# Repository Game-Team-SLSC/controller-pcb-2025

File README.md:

# Game Team's controller PCB for Eurobot Junior 2025

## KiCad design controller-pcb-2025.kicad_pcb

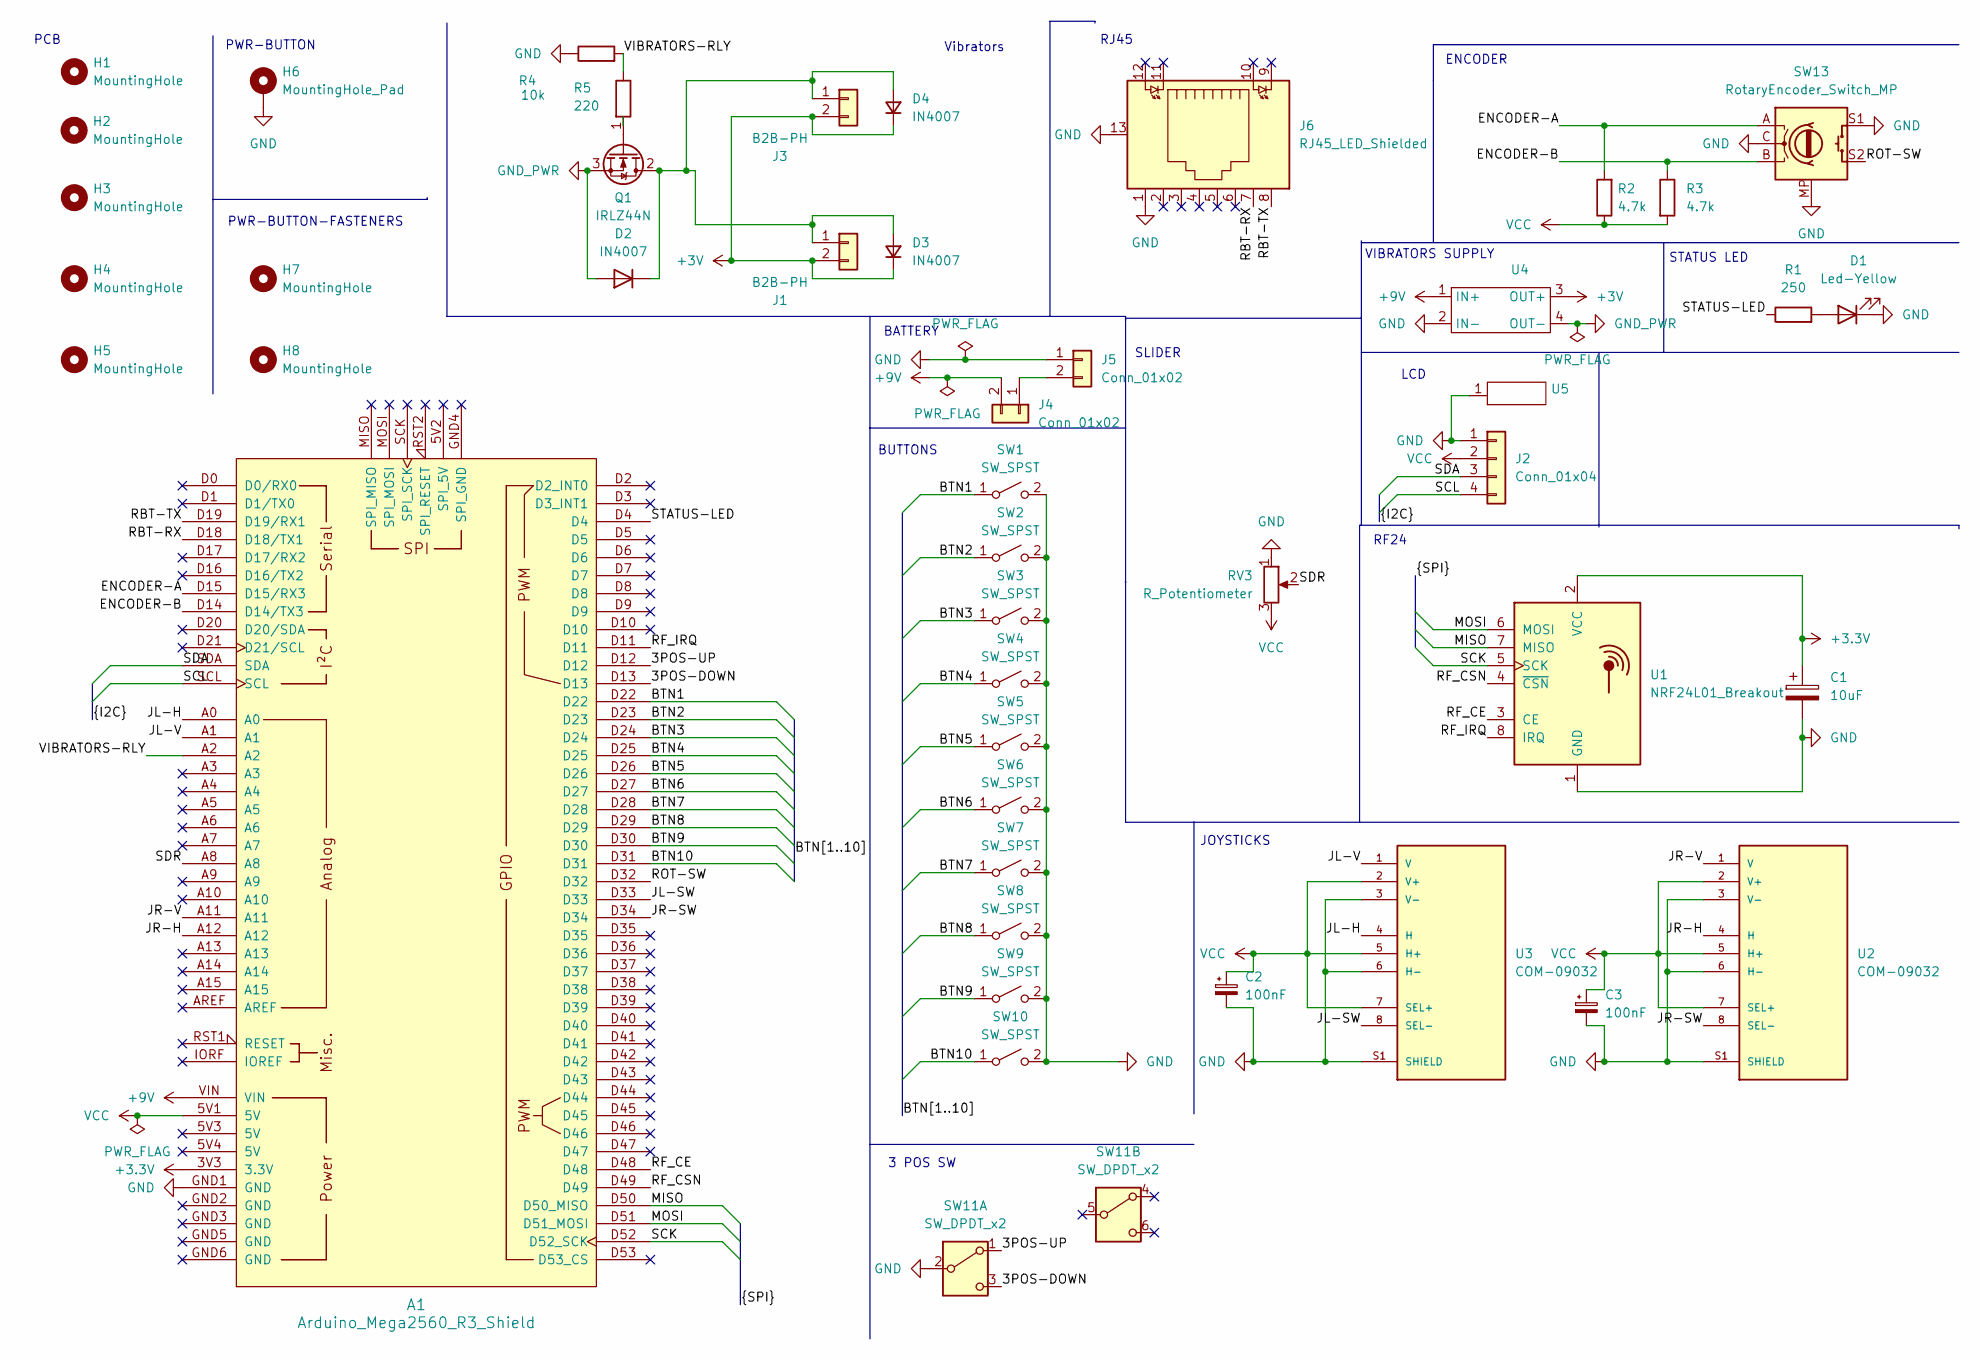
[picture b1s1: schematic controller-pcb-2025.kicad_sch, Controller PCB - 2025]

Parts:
A1: Arduino_Mega2560_R3_Shield; Arduino_Mega2560_R3_Shield_No-MH
C1: 10uF; CP_Radial_D5.0mm_P2.00mm
C2, C3: 100nF
D1: Led-Yellow; LED_D5.0mm
D2: IN4007; D_A-405_P7.62mm_Horizontal
D3, D4: IN4007
H1, H2, H3, H4, H5, H7, H8: MountingHole; MountingHole_2.7mm_M2.5
H6: MountingHole_Pad; Pwr-button_LED
J1, J3: B2B-PH; JST_PH_B2B-PH-K_1x02_P2.00mm_Vertical
J2: Conn_01x04; JST_PH_B4B-PH-K_1x04_P2.00mm_Vertical
J4: Conn_01x02; JST_PH_B2B-PH-K_1x02_P2.00mm_Vertical
J5: Conn_01x02; AMASS_XT30UPB-M_1x02_P5.0mm_Vertical
J6: RJ45_LED_Shielded; RJ45_Cetus_J1B1211CCD_Horizontal-3D-model
Q1: IRLZ44N; TO-220-3_Horizontal_TabDown
R1: 250; R_Axial_DIN0207_L6.3mm_D2.5mm_P7.62mm_Horizontal
R2, R3: 4.7k; R_Axial_DIN0207_L6.3mm_D2.5mm_P7.62mm_Horizontal
R4: 10k; R_Axial_DIN0207_L6.3mm_D2.5mm_P7.62mm_Horizontal
R5: 220; R_Axial_DIN0207_L6.3mm_D2.5mm_P7.62mm_Horizontal
RV3: R_Potentiometer; F2031N
SW1, SW2, SW3, SW4, SW5, SW6, SW7, SW8, SW9, SW10: SW_SPST; ADA1502
SW11: SW_DPDT_x2; KCD2
SW13: RotaryEncoder_Switch_MP; RotaryEncoder_Alps_EC11E-Switch_Vertical_H20mm-3D-model
U1: NRF24L01_Breakout; nRF24L01+_Breakout
U2, U3: COM-09032; XDCR_COM-09032; PARTREV N/A
U4: LM2596
U5: DFR0555

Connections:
+3.3V: A1.3V3 (3.3V), C1.1, U1.2 (VCC)
+3V: D3.1 (K), D4.1 (K), J1.2, J3.2, U4.3 (OUT+)
+9V: A1.VIN, J4.2, U4.1 (IN+)
/3POS-DOWN: A1.D13, SW11.3 (C)
/3POS-UP: A1.D12, SW11.1 (A)
/BTN1: A1.D22, SW1.1 (A)
/BTN2: A1.D23, SW2.1 (A)
/BTN3: A1.D24, SW3.1 (A)
/BTN4: A1.D25, SW4.1 (A)
/BTN5: A1.D26, SW5.1 (A)
/BTN6: A1.D27, SW6.1 (A)
/BTN7: A1.D28, SW7.1 (A)
/BTN8: A1.D29, SW8.1 (A)
/BTN9: A1.D30, SW9.1 (A)
/BTN10: A1.D31, SW10.1 (A)
/ENCODER-A: A1.D15 (D15/RX3), R2.2, SW13.A
/ENCODER-B: A1.D14 (D14/TX3), R3.1, SW13.B
/JL-H: A1.A0, U3.4 (H)
/JL-SW: A1.D33, U3.8 (SEL-)
/JL-V: A1.A1, U3.1 (V)
/JR-H: A1.A12, U2.4 (H)
/JR-SW: A1.D34, U2.8 (SEL-)
/JR-V: A1.A11, U2.1 (V)
/MISO: A1.D50 (D50_MISO), U1.7 (MISO)
/MOSI: A1.D51 (D51_MOSI), U1.6 (MOSI)
/RBT-RX: A1.D18 (D18/TX1), J6.7
/RBT-TX: A1.D19 (D19/RX1), J6.8
/RF_CE: A1.D48, U1.3 (CE)
/RF_CSN: A1.D49, U1.4 (~CSN)
/RF_IRQ: A1.D11, U1.8 (IRQ)
/ROT-SW: A1.D32, SW13.S2
/SCK: A1.D52 (D52_SCK), U1.5 (SCK)
/SCL: A1.SCL, J2.4
/SDA: A1.SDA, J2.3
/SDR: A1.A8, RV3.2
/STATUS-LED: A1.D4, R1.1
/VIBRATORS-RLY: A1.A2, R4.2, R5.1
unnamed: D1.2 (A), R1.2
unnamed: D2.1 (K), D3.2 (A), D4.2 (A), J1.1, J3.1, Q1.2 (D)
unnamed: J4.1, J5.2
unnamed: Q1.1 (G), R5.2
VCC: A1.5V1 (5V), C2.1, C3.1, J2.2, R2.1, R3.2, RV3.3, U2.2 (V+), U2.5 (H+), U2.7 (SEL+), U3.2 (V+), U3.5 (H+), U3.7 (SEL+)

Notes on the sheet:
PWR-BUTTON
BUTTONS
BATTERY
3 POS SW
Vibrators
LCD
PCB
VIBRATORS SUPPLY
PWR-BUTTON-FASTENERS
RJ45
RF24
JOYSTICKS
SLIDER
ENCODER
STATUS LED

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
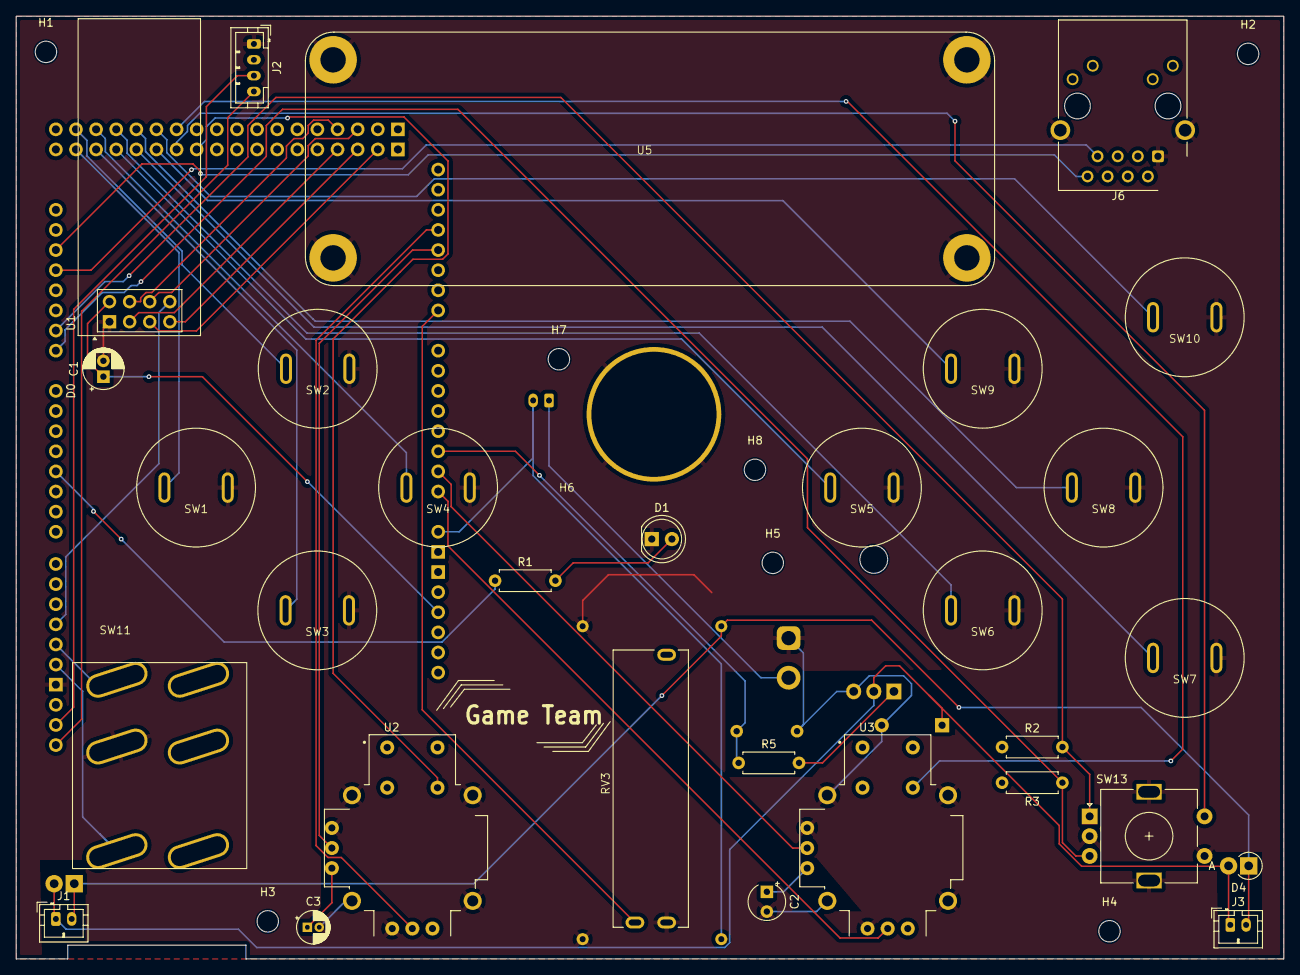
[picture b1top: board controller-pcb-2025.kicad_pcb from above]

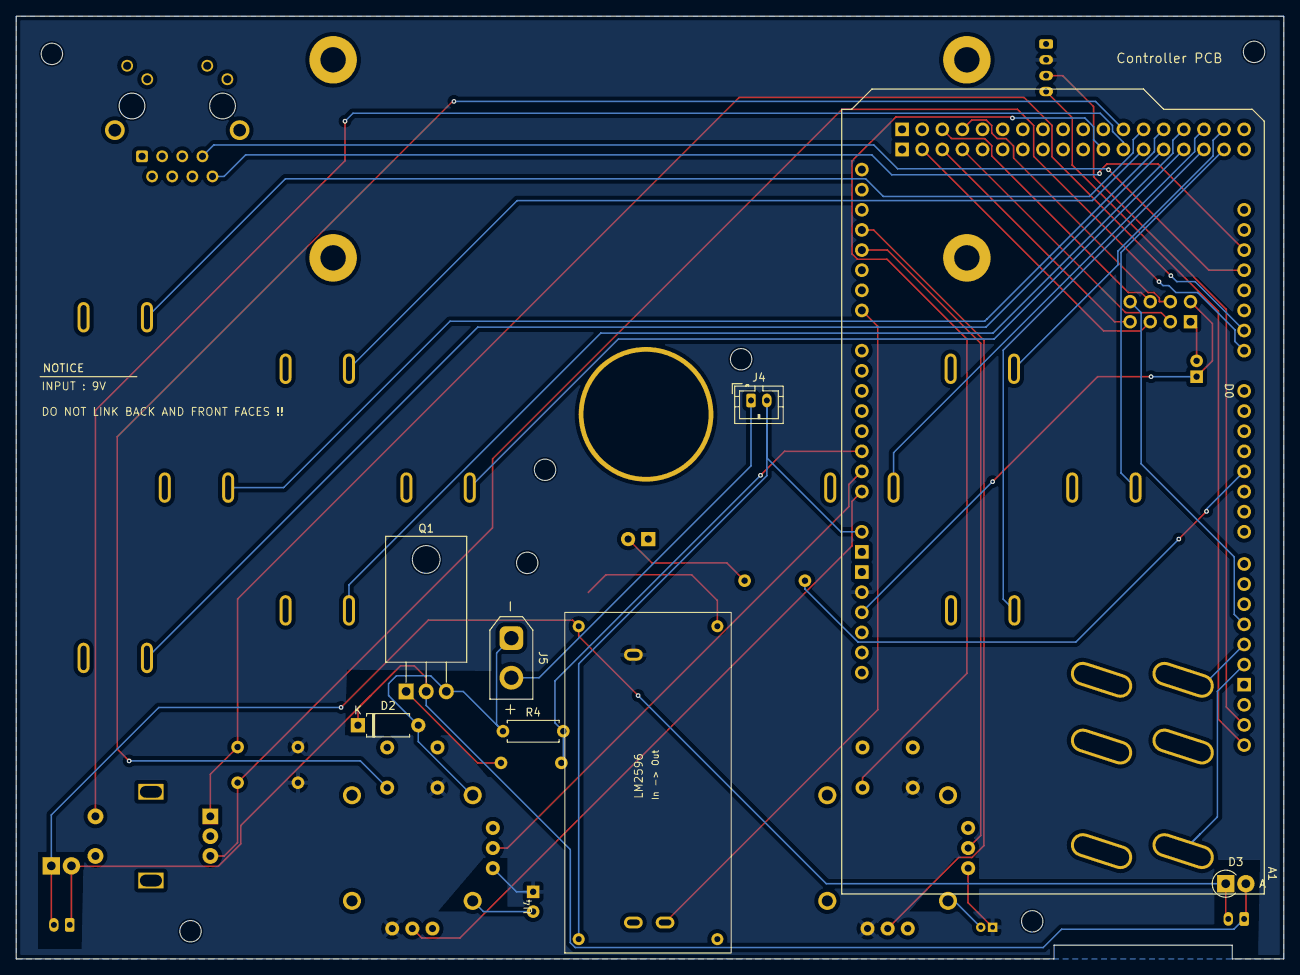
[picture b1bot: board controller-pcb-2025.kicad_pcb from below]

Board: 2 copper layers, 160.0 x 119.0 mm, 46 parts (7 on the bottom side), 43 nets.

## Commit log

2025-01-28 add previews
2025-02-01 Fixes
2025-02-06 run to fab
